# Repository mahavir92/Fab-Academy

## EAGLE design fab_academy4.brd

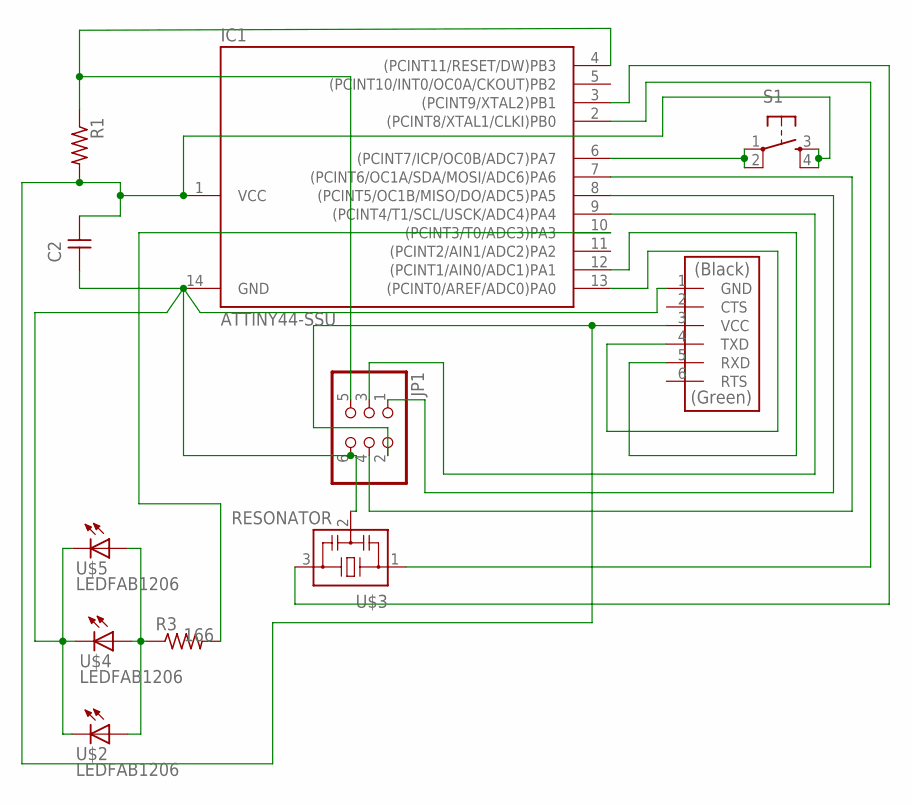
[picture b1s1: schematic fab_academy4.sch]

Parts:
C2: CAP-UNPOLARIZEDFAB; C1206FAB
IC1: ATTINY44-SSU; SOIC14
JP1: PINHD-2X3-SMD; 2X03SMD
R1, R3: RES-US1206FAB; R1206FAB
S1: 6MM_SWITCH6MM_SWITCH; 6MM_SWITCH
U$1: FTDI-SMD-HEADER; 1X06SMD
U$2, U$4, U$5: LEDFAB1206; LED1206FAB
U$3: RESONATOR; EFOBM

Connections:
unnamed: R3.1, U$2.1 (A), U$4.1 (A), U$5.1 (A)
unnamed: IC1.4 ((PCINT11/RESET/DW)PB3), JP1.5, R1.1
unnamed: C2.2, IC1.1 (VCC), JP1.2, R1.2, S1.3 (S), S1.4 (S1), U$1.3 (VCC)
unnamed: IC1.2 ((PCINT8/XTAL1/CLKI)PB0), U$3.1
unnamed: IC1.3 ((PCINT9/XTAL2)PB1), U$3.3
unnamed: IC1.7 ((PCINT6/OC1A/SDA/MOSI/ADC6)PA6), JP1.4
unnamed: IC1.8 ((PCINT5/OC1B/MISO/DO/ADC5)PA5), JP1.1
unnamed: IC1.9 ((PCINT4/T1/SCL/USCK/ADC4)PA4), JP1.3
unnamed: IC1.12 ((PCINT1/AIN0/ADC1)PA1), U$1.5 (RXD)
unnamed: IC1.13 ((PCINT0/AREF/ADC0)PA0), U$1.4 (TXD)
unnamed: C2.1, IC1.14 (GND), JP1.6, U$1.1 (GND), U$2.2 (C), U$3.2, U$4.2 (C), U$5.2 (C)
unnamed: IC1.6 ((PCINT7/ICP/OC0B/ADC7)PA7), S1.1, S1.2 (P1)
unnamed: IC1.10 ((PCINT3/T0/ADC3)PA3), R3.2

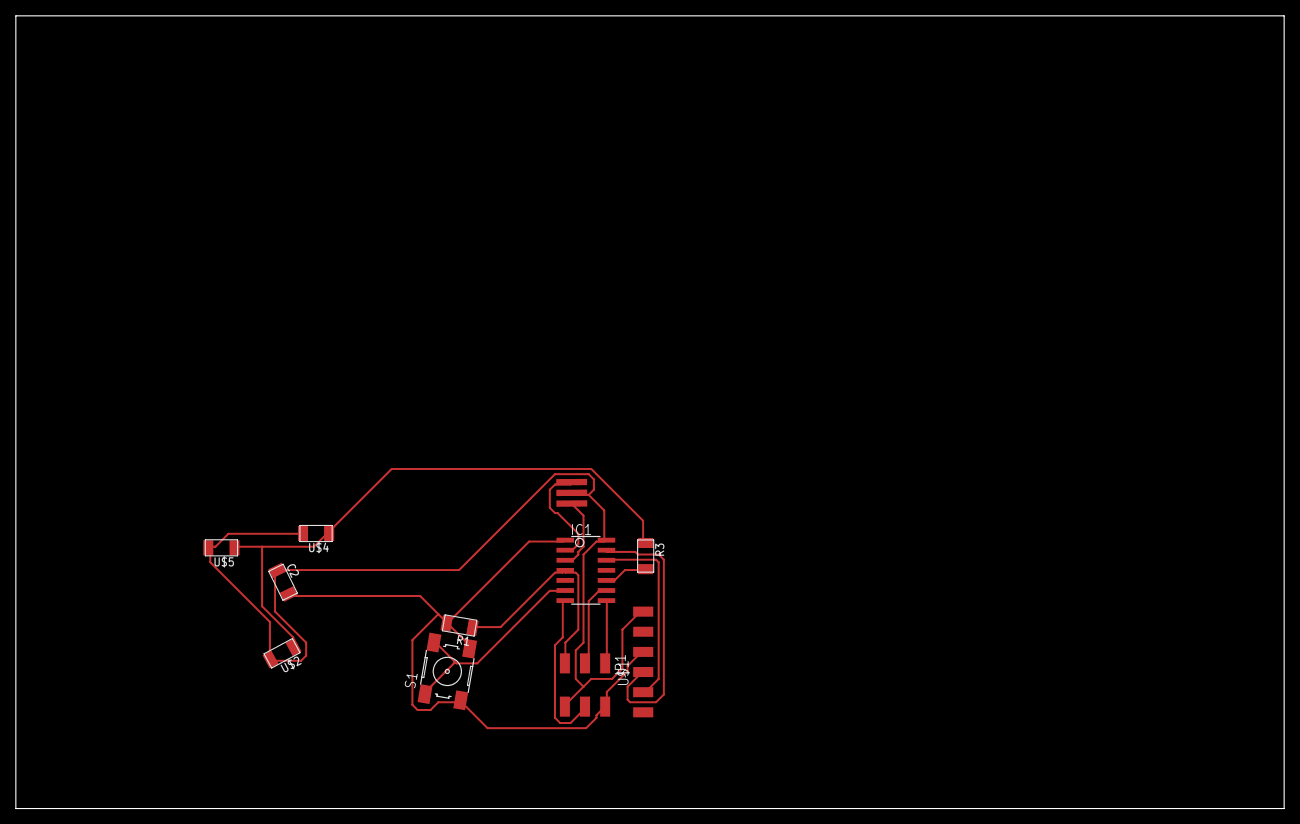
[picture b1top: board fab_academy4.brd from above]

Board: 2 copper layers, 160.0 x 100.0 mm, 11 parts (0 on the bottom side), 13 nets.

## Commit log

2017-03-21 Arduino IDE File
2017-03-21 Firefly file to make Arduino link blink
